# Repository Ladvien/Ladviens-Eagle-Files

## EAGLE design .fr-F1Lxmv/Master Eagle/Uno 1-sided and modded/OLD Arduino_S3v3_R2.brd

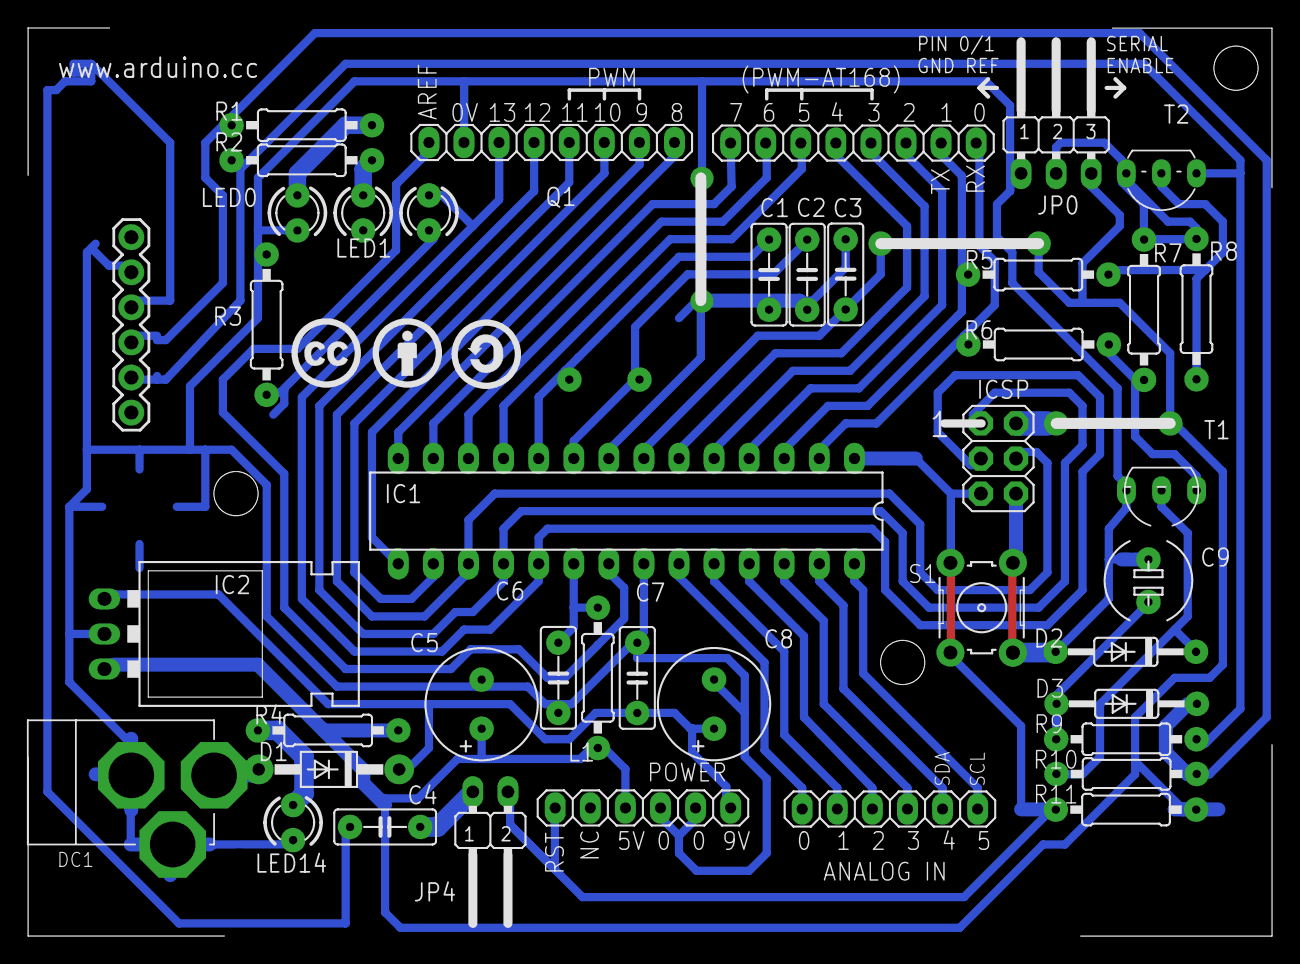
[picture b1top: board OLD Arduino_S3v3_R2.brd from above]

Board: 2 copper layers, 90.1 x 65.7 mm, 46 parts (1 on the bottom side), 42 nets.

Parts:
C1, C2: 22p; C050-025X075
C3, C4, C6, C7: 100n; C050-025X075
C5, C8: 100u; E3,5-8
C9: 10u; E5-6
D1: 1N4004; DO41-10
D2, D3: 1N4148; DO35-10
DC1: DC21MMX; DC-21MM
IC1: ATMEGA8 (OR 168); DIL28-3
IC2: 78XXL
ICSP: ICSP; 2X03
J1: PORT D(D0-D7); 1X08
J2: PORT C(A0-A5); 1X06
J3: PORT B(D8-D13); 1X08
JP0: JP2W
JP4: AUTO RESET; JP1W
L1: 100uH; 0207/10
LED0: RX; LED3MM
LED1: TX; LED3MM
LED13: L; LED3MM
LED14: POWER LED; LED3MM
POWER: 1X06
Q1: 16000; Q
R1, R2: 1K; 0207/10
R3, R4, R6: 1k; 0207/10
R5, R7, R8, R10, R11: 10k; 0207/10
R9: 4k7; 0207/10
S1: B3F-10XX
T1: BC547; TO92
T2: BC557; TO92-EBC
U$1: CC
U$2: BY
U$3: SA
X1: FTDI_BASIC

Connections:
+5V: C3.1, C5.+, IC1.7, IC2.OUT, ICSP.2, JP0.3, L1.2, POWER.3, R4.2, R11.2
AREF: IC1.21, J3.8
GND: C1.1, C2.1, C3.2, C5.-, C6.2, C7.1, C8.-, C9.+, D2.A, DC1.1, DC1.3, IC1.8, IC1.22, IC2.GND, ICSP.6, J3.7, JP0.1, LED0.K, LED1.K, LED14.K, POWER.4, POWER.5, R3.1, S1.1, S1.2, T1.1, X1.CTS
M8RXD: IC1.2, J1.1, R6.1
M8TXD: IC1.3, J1.2, R5.1
unnamed: IC1.18, ICSP.1, J3.5
unnamed: C9.-, D3.A, R9.1
unnamed: LED14.A, R4.1
unnamed: IC1.17, ICSP.4, J3.4
unnamed: IC1.14, J3.1
unnamed: C1.2, IC1.9, Q1.1
unnamed: C2.2, IC1.10, Q1.2
unnamed: D1.A, DC1.2
unnamed: IC1.4, J1.3
unnamed: IC1.5, J1.4
unnamed: IC1.6, J1.5
unnamed: IC1.11, J1.6
unnamed: IC1.12, J1.7
unnamed: IC1.13, J1.8
unnamed: IC1.23, J2.1
unnamed: IC1.24, J2.2
unnamed: IC1.25, J2.3
unnamed: IC1.26, J2.4
unnamed: IC1.27, J2.5
unnamed: IC1.28, J2.6
unnamed: IC1.15, J3.2
unnamed: IC1.16, J3.3
unnamed: D3.C, R1.2, R10.2, X1.TXO
unnamed: R6.2, R7.1, T1.3
unnamed: R5.2, R8.2, T2.B
unnamed: D2.C, R10.1, T1.2
unnamed: LED13.K, R3.2
unnamed: LED1.A, R2.1
unnamed: LED0.A, R1.1
unnamed: C4.1, JP4.2
unnamed: C4.2, X1.VCC
unnamed: R2.2, R9.2, T2.C, X1.RXI
unnamed: C6.1, IC1.20, L1.1
RESET: IC1.1, ICSP.5, JP4.1, POWER.1, R11.1, S1.3, S1.4
SCK: IC1.19, ICSP.3, J3.6, LED13.A
SERIAL_VCC: JP0.2, R7.2, R8.1, T2.E
VIN: C7.2, C8.+, D1.C, IC2.IN, POWER.6

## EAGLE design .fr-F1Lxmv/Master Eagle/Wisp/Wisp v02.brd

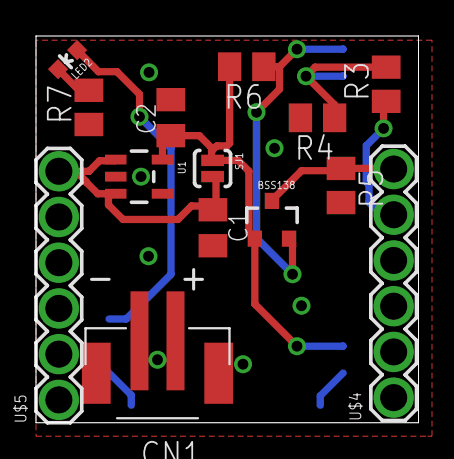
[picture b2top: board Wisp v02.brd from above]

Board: 2 copper layers, 21.2 x 21.5 mm, 15 parts (1 on the bottom side), 9 nets.

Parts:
BSS138: MOSFET-NCHANNELSMD; SOT23-3
C1, C2: 1uF; C0805K
CN1: JST-PH-2-SMT
LED2: LED-0603
R3, R4, R5, R6: 10k; M0805
R7: 220; M0805
SJ1: SOLDERJUMPERNO; SJ_2S-NO
U1: V_REG_LDOSMD; SOT23-5
U$1: BLE-HM-10
U$4, U$5: 1X6_SHORT_ROUND

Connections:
3_3V: BSS138.1, C2.1, R6.2, SJ1.1, U1.5, U$1.3.3V
GND: C1.2, C2.2, R4.2, R7.1, U1.2, U$1.GND1, U$1.GND2, U$1.GND3, U$1.GND4, U$5.5
HVTX->LVRX: R3.2, R4.1, U$1.UART_RX
LVRX->HVTX: BSS138.2, R6.1, U$1.UART_TX
unnamed: LED2.A, U$1.PIO1
unnamed: LED2.C, R7.2
RAW: C1.1, SJ1.2, U1.1, U1.3, U$5.6
RX_HV: BSS138.3, R5.1, U$4.6
TX_HV: R3.1, U$4.5

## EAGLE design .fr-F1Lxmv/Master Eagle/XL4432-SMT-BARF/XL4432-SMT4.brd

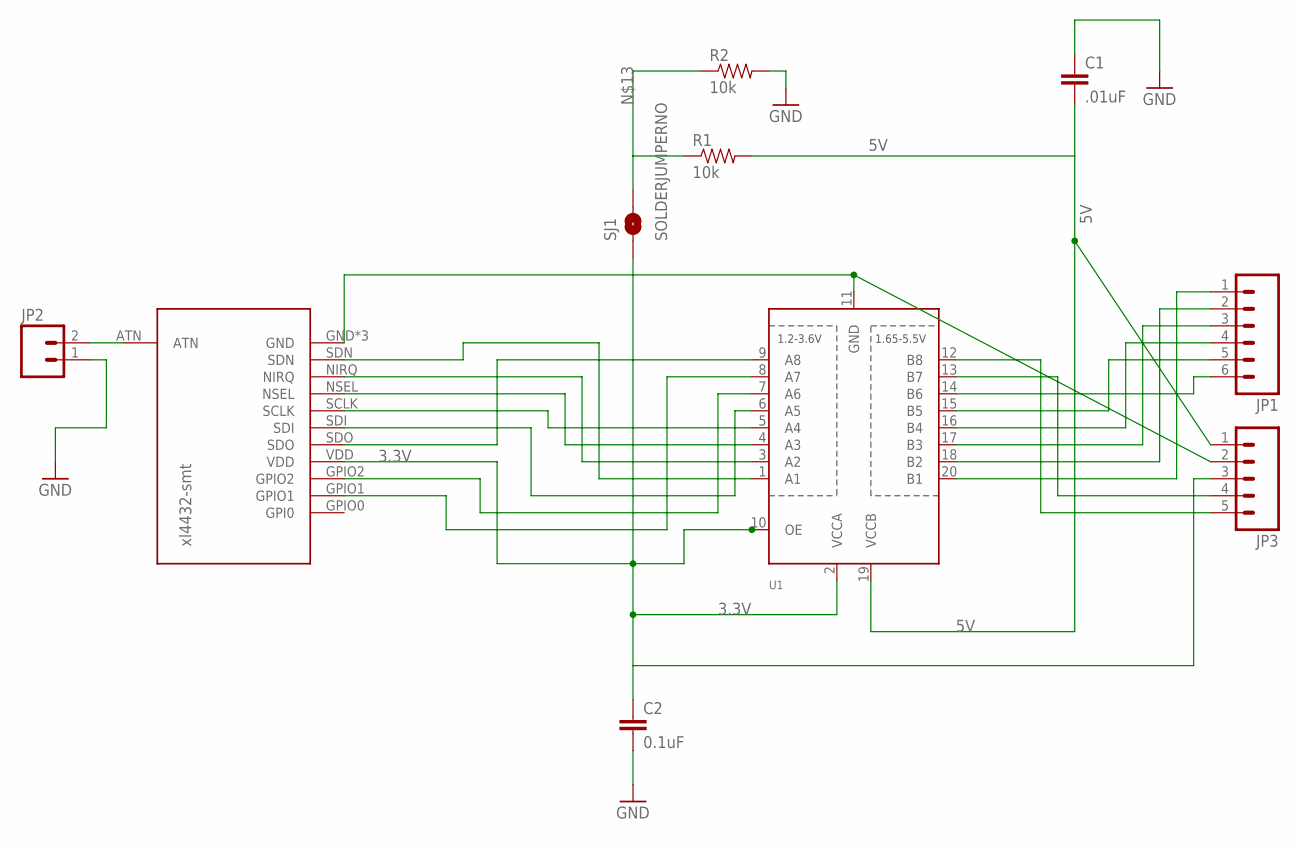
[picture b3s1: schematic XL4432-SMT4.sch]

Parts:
C1: .01uF; 0805
C2: 0.1uF; 0805
JP1: M06LOCK; 1X06_LOCK
JP2: M02LOCK; 1X02_LOCK
JP3: M05LOCK; 1X05_LOCK
R1, R2: 10k; 0805
SJ1: SOLDERJUMPERNO; SJ_2S-NO
U1: TXB0108PWR; TSSOP20
U$1: XL4432-SMT

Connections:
3.3V: C2.1, JP3.3, SJ1.1, U1.2 (VCCA), U1.10 (OE), U$1.VDD
5V: C1.2, JP3.1, R1.2, U1.19 (VCCB)
GND: C1.1, C2.2, JP2.1, JP3.2, R2.2, U1.11 (GND), U$1.GND, U$1.GND1 (GND), U$1.GND3 (GND)
H-SDN: JP1.1, U1.20 (B1)
L-SDN: U1.1 (A1), U$1.SDN
unnamed: U1.9 (A8), U$1.SDO
unnamed: U1.3 (A2), U$1.NIRQ
unnamed: U1.4 (A3), U$1.NSEL
unnamed: U1.5 (A4), U$1.SCLK
unnamed: U1.6 (A5), U$1.SDI
unnamed: U1.7 (A6), U$1.GPIO2
unnamed: U1.8 (A7), U$1.GPIO1
unnamed: JP1.2, U1.18 (B2)
unnamed: JP2.2, U$1.ATN
unnamed: R1.1, R2.1, SJ1.2
unnamed: JP1.3, U1.17 (B3)
unnamed: JP1.4, U1.16 (B4)
unnamed: JP1.5, U1.15 (B5)
unnamed: JP1.6, U1.14 (B6)
unnamed: JP3.4, U1.13 (B7)
unnamed: JP3.5, U1.12 (B8)

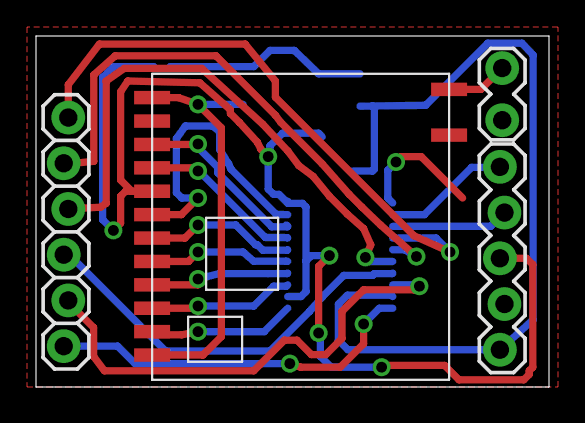
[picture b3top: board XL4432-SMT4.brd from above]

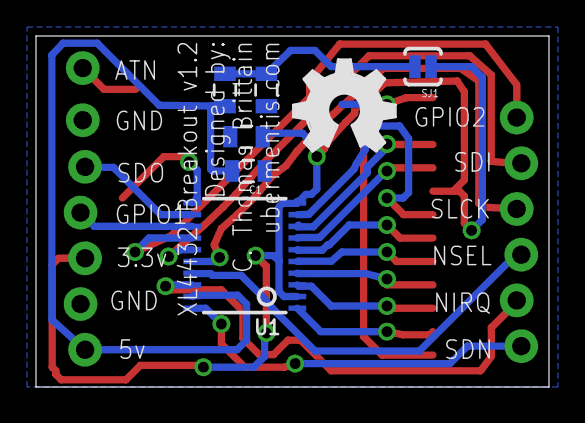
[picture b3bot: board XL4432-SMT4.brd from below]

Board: 2 copper layers, 28.5 x 19.5 mm, 11 parts (7 on the bottom side), 21 nets.

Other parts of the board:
U$3: OSHW_FILLX200_NOTEXT

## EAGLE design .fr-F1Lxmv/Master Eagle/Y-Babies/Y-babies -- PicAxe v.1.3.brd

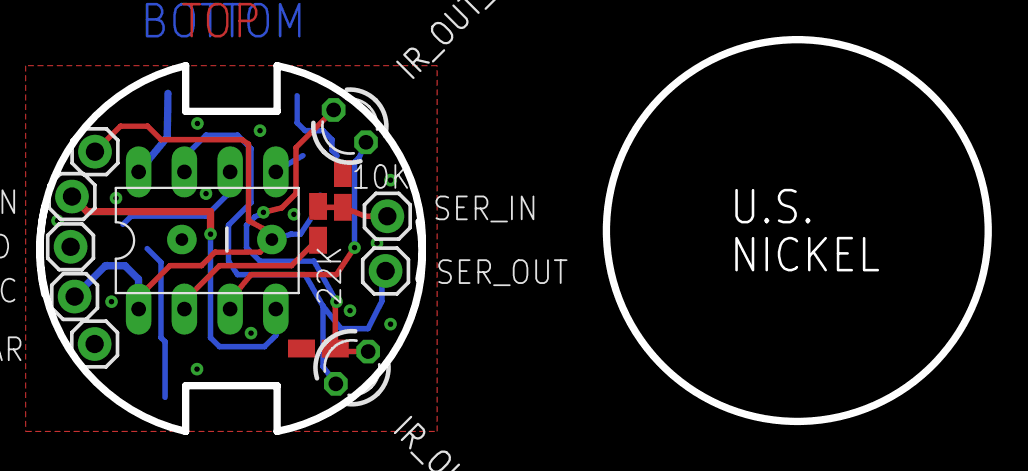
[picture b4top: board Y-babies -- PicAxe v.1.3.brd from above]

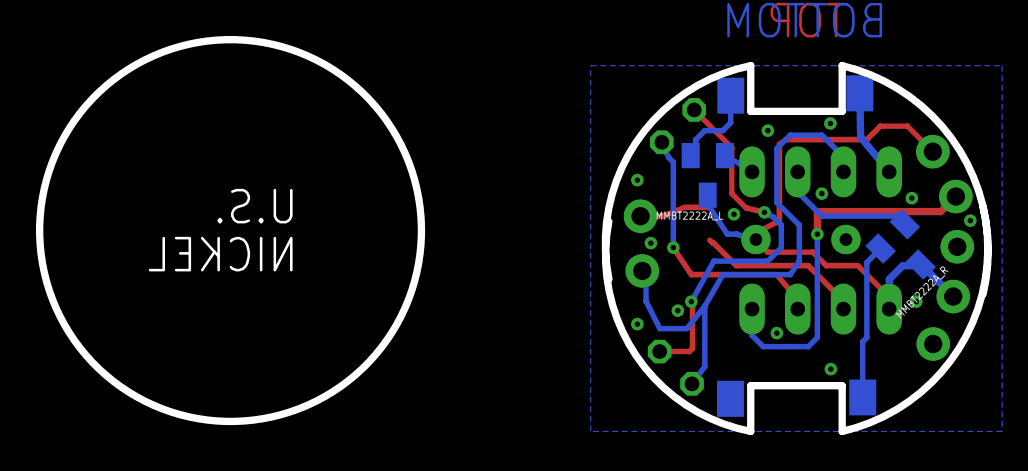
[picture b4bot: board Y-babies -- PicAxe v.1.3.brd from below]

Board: 2 copper layers, 52.7 x 21.8 mm, 20 parts (6 on the bottom side), 12 nets.

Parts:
10K, 22K: R0805W
C1: CAP-PTH-5MM
GND: M01PTH; 1X01
GND_BAR: M01PTH; 1X01
IR_IN: M01PTH; 1X01
IR_OUT_A: LED3MM
IR_OUT_B: LED3MM
MMBT2222A_L, MMBT2222A_R: SOT23
MOT_1_A, MOT_1_B, MOT_2_A, MOT_2_B: M01SMD-4.5X1.5; PAD-1.5X4.5
PICAXE-08M2: PICAXE-08M2; DIL8
R2: R0805W
SER_IN: M01PTH; 1X01
SER_OUT: M01PTH; 1X01
VCC: M01PTH; 1X01
VCC_BAR: M01PTH; 1X01

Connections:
GND: 10K.2, C1.1, GND.1, GND_BAR.1, MOT_1_A.P$1, MOT_2_B.P$1, PICAXE-08M2.8, R2.2
unnamed: MMBT2222A_L.1, PICAXE-08M2.5
unnamed: MMBT2222A_R.1, PICAXE-08M2.6
unnamed: IR_OUT_B.A, PICAXE-08M2.7, SER_OUT.1
unnamed: 10K.1, 22K.2, SER_IN.1
unnamed: IR_OUT_A.A, PICAXE-08M2.3
unnamed: IR_OUT_A.K, IR_OUT_B.K, R2.1
unnamed: 22K.1, PICAXE-08M2.2
unnamed: MMBT2222A_L.2, MOT_1_B.P$1
unnamed: MMBT2222A_R.2, MOT_2_A.P$1
unnamed: IR_IN.1, PICAXE-08M2.4
VCC: C1.2, MMBT2222A_L.3, MMBT2222A_R.3, PICAXE-08M2.1, VCC.1, VCC_BAR.1

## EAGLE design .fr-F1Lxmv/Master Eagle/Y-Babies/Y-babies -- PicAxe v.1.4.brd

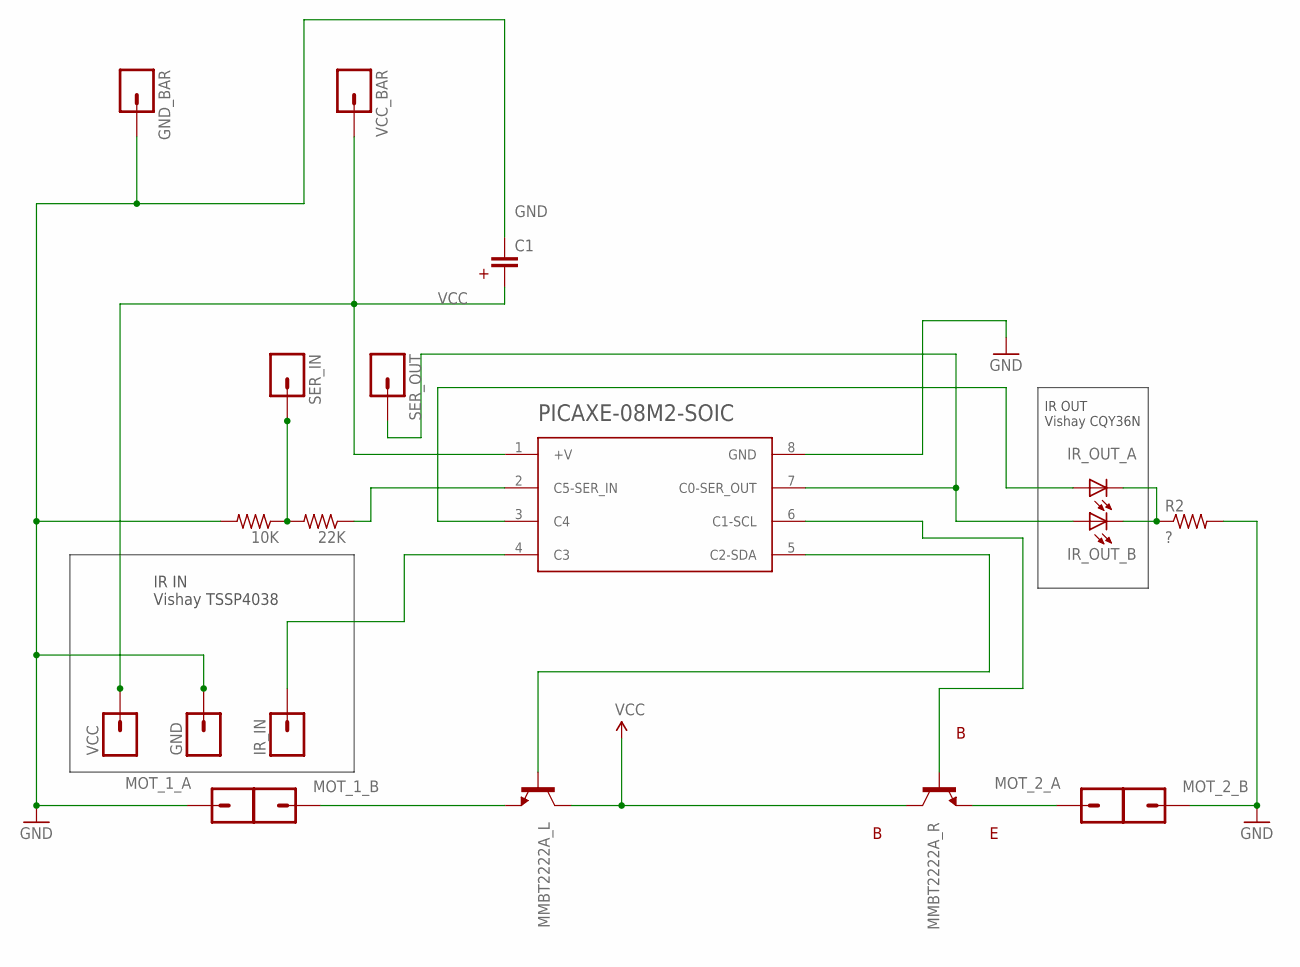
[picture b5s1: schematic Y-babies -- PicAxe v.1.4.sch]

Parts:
10K, 22K: R-US_R0402; R0402
C1: CAPPTH1; CAP-PTH-5MM
GND: M01PTH; 1X01
GND_BAR: M01PTH; 1X01
IR_IN: M01PTH; 1X01
IR_OUT_A: LED3MM
IR_OUT_B: LED3MM
MMBT2222A_L, MMBT2222A_R: TRANSISTOR_NPNSOT23; SOT23
MOT_1_A, MOT_1_B, MOT_2_A, MOT_2_B: M01SMD-4.5X1.5; PAD-1.5X4.5
R2: ?; R0402
SER_IN: M01SMD-4.5X1.5; PAD-1.5X4.5
SER_OUT: M01SMD-4.5X1.5; PAD-1.5X4.5
U$1: PICAXE-08M2_SOIC; SOIC8
VCC: M01PTH; 1X01
VCC_BAR: M01PTH; 1X01

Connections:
E: MMBT2222A_R.2 (E), MOT_2_A.P$1
GND: 10K.2, C1.1, GND.1, GND_BAR.1, MOT_1_A.P$1, MOT_2_B.P$1, R2.2, U$1.8 (GND)
unnamed: MMBT2222A_L.1 (B), U$1.5 (C2-SDA)
unnamed: MMBT2222A_R.1 (B), U$1.6 (C1-SCL)
unnamed: IR_OUT_B.A, SER_OUT.P$1, U$1.7 (C0-SER_OUT)
unnamed: 10K.1, 22K.2, SER_IN.P$1
unnamed: IR_OUT_A.A, U$1.3 (C4)
unnamed: IR_OUT_A.K (C), IR_OUT_B.K (C), R2.1
unnamed: 22K.1, U$1.2 (C5-SER_IN)
unnamed: MMBT2222A_L.2 (E), MOT_1_B.P$1
unnamed: IR_IN.1, U$1.4 (C3)
VCC: C1.2, MMBT2222A_L.3 (C), MMBT2222A_R.3 (C), U$1.1 (+V), VCC.1, VCC_BAR.1

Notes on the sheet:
IR IN Vishay TSSP4038
IR OUT Vishay CQY36N

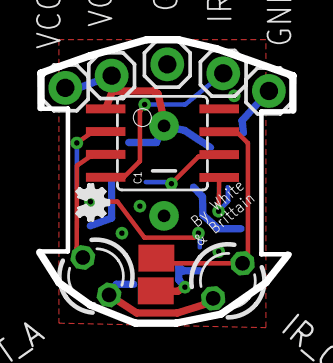
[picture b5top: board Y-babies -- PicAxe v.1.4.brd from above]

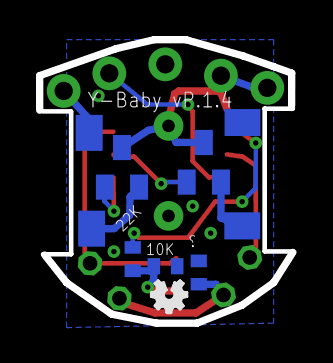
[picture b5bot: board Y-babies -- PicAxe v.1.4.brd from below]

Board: 2 copper layers, 14.1 x 15.8 mm, 22 parts (10 on the bottom side), 12 nets.

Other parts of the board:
U$3, U$4: OSHW_FILLX70_NOTEXT

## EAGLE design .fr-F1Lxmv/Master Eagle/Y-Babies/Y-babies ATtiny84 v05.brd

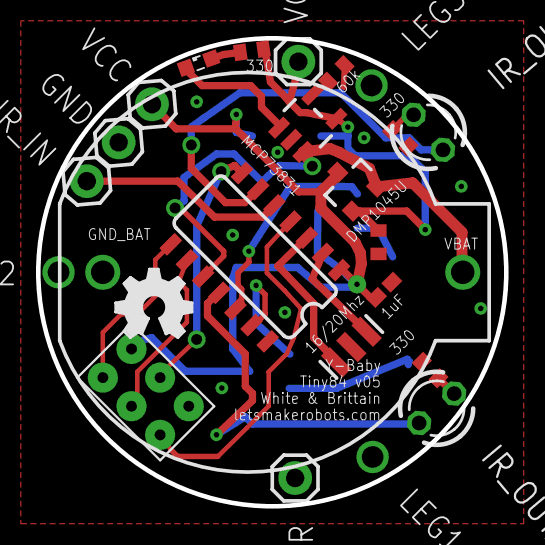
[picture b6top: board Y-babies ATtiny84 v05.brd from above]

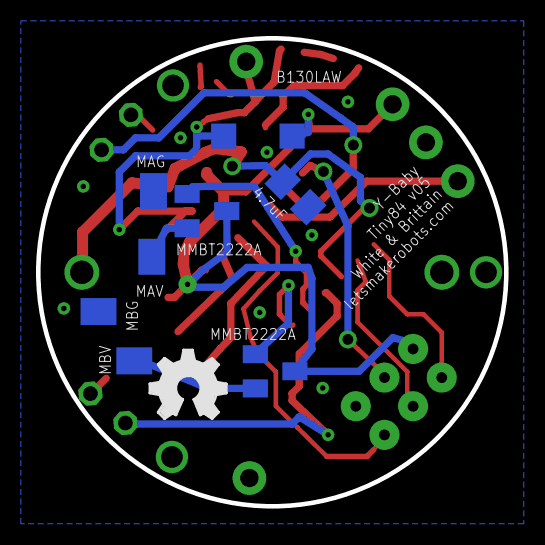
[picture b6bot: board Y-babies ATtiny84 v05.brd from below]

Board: 2 copper layers, 26.0 x 26.0 mm, 30 parts (9 on the bottom side), 22 nets.

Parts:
BAT1: LIR2032; BATTCOM_20MM_PTH
C1: 1uF; C0402K
C2: 4.7uF; C0805K
D1: B130LAW; SOD123
DMP1045U: MOSFET-PCHANNELSMD; SOT23-3
GND: M01PTH; 1X01
GND_BAR: M01PTH; 1X01
IR_IN: M01PTH; 1X01
IR_OUT_A: LED3MM
IR_OUT_B: LED3MM
LED1: SML0603
MMBT2222A_L, MMBT2222A_R: SOT23
MOT_1_A, MOT_1_B, MOT_2_A, MOT_2_B: M01SMD-4.5X1.5; PAD-1.5X4.5
R1, R2, R3: 330; R0402
R4: 60k; R0402
R5: 100k; R0402
U1: MCP73831; SOT23-5
U$1: ATTINY84; SO14
U$2: POGO_PIN_SPI_PAD
U$3, U$4: OSHW_FILLX150_NOTEXT
VCC: M01PTH; 1X01
VCC_BAR: M01PTH; 1X01
Y1: 16MHz; RESONATOR-SMD

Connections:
5V: D1.A, DMP1045U.1, R3.2, R5.1, U1.4, VCC_BAR.1
GND: BAT1.2, C1.2, C2.2, GND.1, GND_BAR.1, MOT_1_A.P$1, MOT_2_B.P$1, R1.2, R2.2, R4.2, R5.2, U1.2, U$1.14, U$2.GND, Y1.2
IR_IN: IR_IN.1, U$1.5
IR_OUT_A: IR_OUT_A.A, U$1.11
IR_OUT_B: IR_OUT_B.A, U$1.6
MISO: U$1.8, U$2.MISO
MOSI: U$1.7, U$2.MOSI
MOT_B_IN: MMBT2222A_L.2, MOT_1_B.P$1
MOT_B_SIG: MMBT2222A_L.1, U$1.13
M_A_IN: MMBT2222A_R.2, MOT_2_A.P$1
M_A_SIG: MMBT2222A_R.1, U$1.12
unnamed: LED1.C, U1.1
unnamed: LED1.A, R3.1
unnamed: U$1.3, Y1.3
unnamed: U$1.2, Y1.1
unnamed: IR_OUT_A.K, R1.1
unnamed: IR_OUT_B.K, R2.1
unnamed: R4.1, U1.5
RES: U$1.4, U$2.RST
SCK: U$1.9, U$2.SCK
VBAT: BAT1.1, C2.1, DMP1045U.2, U1.3, U$1.10
VCC: C1.1, D1.C, DMP1045U.3, MMBT2222A_L.3, MMBT2222A_R.3, U$1.1, U$2.VCC, VCC.1

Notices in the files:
.fr-F1Lxmv/Master Eagle/Uno 1-sided and modded/OLD Arduino_S3v3_R2.brd:
Released under the Creative Commons Attribution Share-Alike 2.5 License
http://creativecommons.org/licenses/by-sa/2.5
CC BY SA 2.5
parts and their libraries:
SparkFun: Licensing: CC v3.0 Share-Alike You are welcome to use this library for commercial purposes.
microbuilder: This work is placed in the public domain, and may be freely used for commercial and non-commercial work with the following conditions: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
